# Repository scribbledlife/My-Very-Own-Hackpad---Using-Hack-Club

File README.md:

# My Very Own Hackpad (6-Key Macropad)

**Built for Hack Club** 

This is my first ever build from scratch. This is a macropad with 6 keys, made by using the tutorial provided by Hack Club.

My name is **Mridul Goel**, and I am a sophomore. I aspire to be a future aerospace engineer, and as such I thought that it would be a good idea to get into this kind of stuff. What you are looking at is a 6-key macropad that I made for my first ever project, just to get the hang of things and different kinds of softwares that are available.

I mainly used **KiCad** for the schematic and the main PCB wiring. Then I moved onto **Fusion 360**, working on the bottom and top case to house the microcontroller and everything.

**NOTE**: I modified the original design by changing it from 4 keys to 6 keys, because I found out that this is supposed to be modified to be counted as your own—and well, who doesn't like some more keys right! 

## What Everything Is

### 1. Schematic & PCB
This was the first step in making my macropad. You can find the provided screenshots of the Schematic and PCB wiring in the folder named "Screenshots". But below are the images just in case!

### 2. Case_Files
These are the 3D printable files that are going to house the PCB, and all the switches and everything that makes the macropad work.

### 3. Keyboard_Keycaps
These are all the pre-"Case_Files" files which are the dimensions of the actual Cherry MX Keycaps, so that the case actually fits on top of the keys.

### 4. Case Screenshots (Fusion 360)

### 5. main.py
This is the code file for the keyboard, which allows the keyboard to be properly coded and work with my laptop. I lowkey just copied it from the Blueprint guide, but right now I am trying to learn Python fully so that I understand what is going on and can customize it properly.

That is everything in this repository with every file, everything I worked on, and the whole process. I didn't make a journal because it said I don't have to.

# BOM
1 Seeed XIAO RP2040
6 THT 1N4148 Diodes
6 Cherry MX-style switches
6 Keycaps
8 SK6812 MINI-E LEDs
4 Screws
4 Heatset inserts
1 3D printed case (find the CAD files in /case)

Thanks for checking out my project!

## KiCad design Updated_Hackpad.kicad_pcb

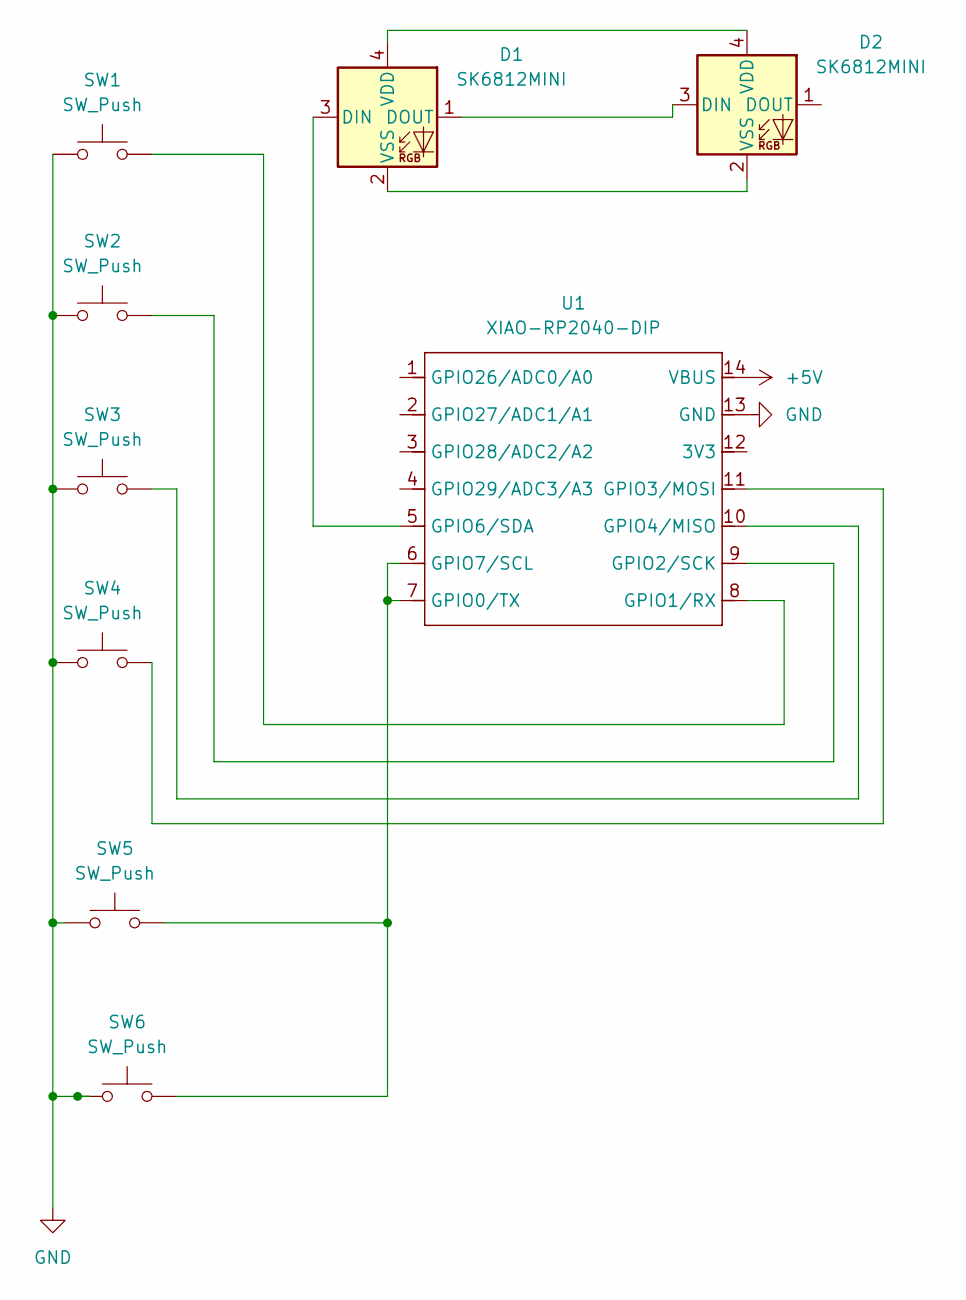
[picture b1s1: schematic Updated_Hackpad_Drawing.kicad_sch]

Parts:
D1, D2: SK6812MINI; LED_SK6812MINI_PLCC4_3.5x3.5mm_P1.75mm
SW1, SW2, SW3, SW4, SW5, SW6: SW_Push; SW_Cherry_MX_1.00u_PCB
U1: XIAO-RP2040-DIP

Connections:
+5V: U1.14 (VBUS)
GND: SW1.1, SW2.1, SW3.1, SW4.1, SW5.1, SW6.1, U1.13 (GND)
unnamed: D1.3 (DIN), U1.5 (GPIO6/SDA)
unnamed: D1.1 (DOUT), D2.3 (DIN)
unnamed: D1.4 (VDD), D2.4 (VDD)
unnamed: D1.2 (VSS), D2.2 (VSS)
unnamed: SW5.2, SW6.2, U1.6 (GPIO7/SCL), U1.7 (GPIO0/TX)
unnamed: SW1.2, U1.8 (GPIO1/RX)
unnamed: SW2.2, U1.9 (GPIO2/SCK)
unnamed: SW4.2, U1.11 (GPIO3/MOSI)
unnamed: SW3.2, U1.10 (GPIO4/MISO)

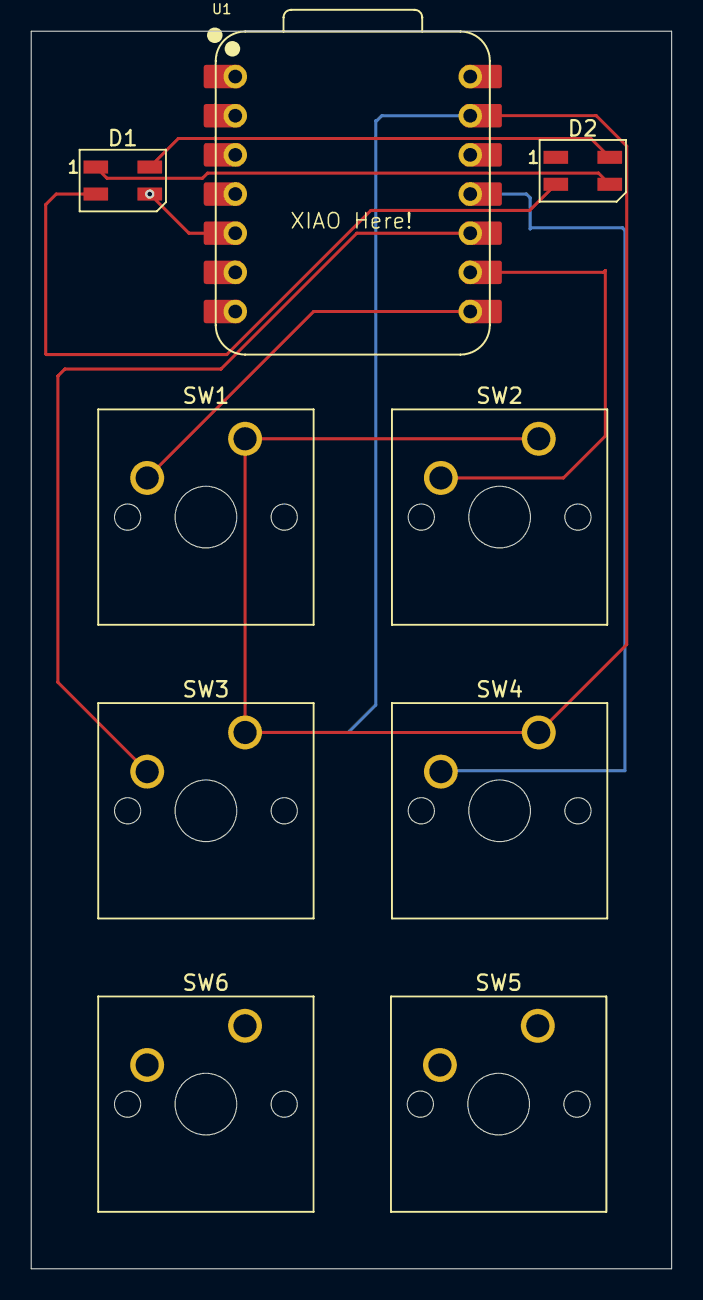
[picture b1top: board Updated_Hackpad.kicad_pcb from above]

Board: 2 copper layers, 41.5 x 80.3 mm, 9 parts (0 on the bottom side), 10 nets.

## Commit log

2025-11-28 Case Files
    These are all the case files that I used to make my macropad. All the .f3d files are the individual bottom and top parts of the case, while the .3mf is the full case with the PCB board inside the act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
2025-11-28 Keyboard / Keycaps Layout
    This is the actual layout that I followed, it has the four keys, and how I cut them out of the actual top part of the case to allow the Cherry MX keys to into the actual case.
2025-11-28 Schematic & PCB
    This was the first part of the process, making the electronics of the actual macropad. As said in the tutorial, I used a XIAO microcontroller, which is an Arduino. I turned the schematic into a PCB s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
2025-11-28 Rename Hackpad.step to Schematic_and_PCB/Hackpad.step
2025-11-28 Rename Mriduls_Hackpad_Keycaps_Cover.f3d to Case_Files/Mriduls_Hackpad_Keycaps_Cover.f3d
2025-11-28 Rename Mriduls_hackpad.3mf to Case_Files/Mriduls_hackpad.3mf
2025-11-28 Rename Mriduls_hackpad.f3d to Case_Files/Mriduls_hackpad.f3d
2025-11-28 Rename plate-2025-11-27T14_27_47.394Z.dxf to Keyboard_Keycaps/plate-2025-11-27T14_27_47.394Z.dxf
2025-12-04 Update README.md
    Images
2025-12-06 Added New Updated Case Files
2025-12-06 Added all the updated drawings and PCB
    There is only one .step, because there is no way for me to export the schematic drawing from KiCad as a .step, so only the circut board is .step
2025-12-06 Rename Hackpad_Updated.step to Schematic_&_PCB/Hackpad_Updated.step
2025-12-06 Rename Updated_Hackpad.kicad_pro to Schematic_&_PCB/Updated_Hackpad.kicad_pro
2025-12-06 Layout For Keys
    This one is lowey wrong, because wrong, but I am too lazy to change, so I didn't use the 3 on the right side, so that I only 6 keys arranged 2x3
2025-12-06 Rename 6-key_layout.dxf to Keycap_Layout/6-key_layout.dxf
2025-12-06 Screenshots of everything
    I'll also put these onto the readme file
2025-12-06 Rename screenshot_PCB.png to Screenshots/Schematic_&_PCB/screenshot_PCB.png
2025-12-06 Rename screenshot_drawing.png to Screenshots/Schematic_&_PCB/screenshot_drawing.png
2025-12-06 Rename screenshot_bottom_case.png to Screenshots/Case_Files/screenshot_bottom_case.png
2025-12-06 Rename screenshot_caseS.png to Screenshots/Case_Files/screenshot_caseS.png
2025-12-06 Rename screenshot_top_case.png to Screenshots/Case_Files/screenshot_top_case.png
2025-12-07 Rename main.py to Firmware/ main.py
